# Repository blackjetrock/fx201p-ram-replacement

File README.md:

# fx201p-ram-replacement
FX201P RAM replacement

A PCB that replaces the RAM in an FX201P. Both HD36106 devices are replaced by an RP2040 based Pico-Zero
module. That replaces the memories and the program RAM. Additional features are added:

* Save program space to RP2040 internal flash
* Load program space from flash
* Save memory space to flash
* Load memory space from flash
* Save all memory to flash
* Load all memory from flash
* Catalog of flash slots.

  The flash has 250 slots, each is big enough to hold the entire RAM of the FX201P.

Command Mechanism
=================

To issue a command to the RP2040, put a number of the following format in M8:

ccsnnn E88

where:
```
cc     Command code
s      Status
nnn    Parameter
```

Command codes:

```
94          Zero all memory (both HD356106 RAM areas, but not flash)
95          Zero memories
96          Zero program space

11          Load program and memory areas from flash slot nnn
12          Load memory area from slot nnn
13          Load program area from slot nnn

15          Save program and memory areas to flash slot nnn
16          Save memory area to flash slot nnn
17          Save program area to flash slot nnn

47          Shows empty flash slots as a bitmap in octal in M9 A 1 denotes a non-blank slot
```

USB Interface
=============

The USB of the Pio-Zero has a menu driven interface.

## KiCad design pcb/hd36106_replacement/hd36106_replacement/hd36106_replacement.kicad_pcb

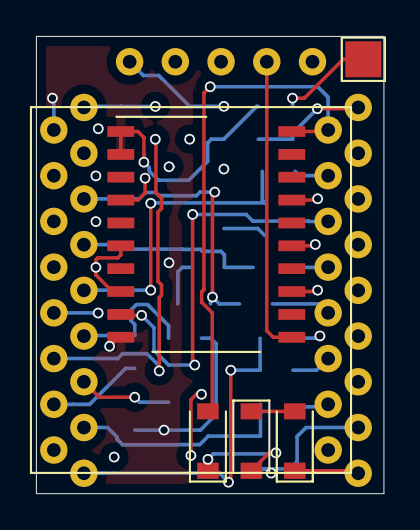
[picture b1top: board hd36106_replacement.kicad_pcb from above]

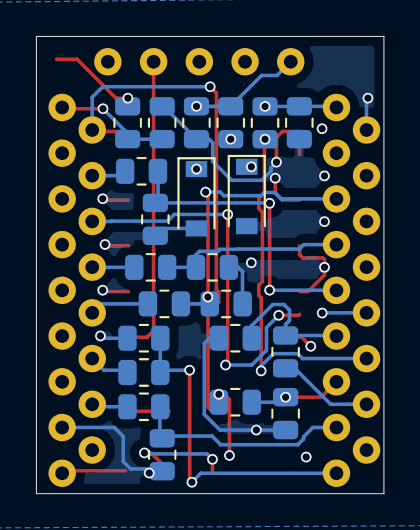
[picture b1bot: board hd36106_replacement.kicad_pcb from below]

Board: 4 copper layers, 19.3 x 25.4 mm, 29 parts (22 on the bottom side), 27 nets.

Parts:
D1: 4148; D_SOD-123
D2, D3: Schottky; D_SOD-123
D4, D5: SS36; D_SOD-123
J1: Conn_01x01_Male; TestPoint_Pad_2.0x2.0mm
R1, R2, R3, R4, R5, R6, R7, R8, R9, R10, R11, R12, R13, R14, R15, R16, R17, R18: 10k; R_0805_2012Metric
R27, R28: R_Small; R_0805_2012Metric
U1: rp2040-zero
U2: 40244; SO-20_12.8x7.5mm_P1.27mm
U3: HD36106; tc5006p

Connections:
6V4: D1.2, U2.20, U3.16
A0: R3.2, R4.1, U1.23
A1: R1.2, R2.1, U1.22
A2: R13.2, R14.1, U1.21
A3: R11.2, R12.1, U1.20
CE: R5.2, R6.1, U1.17
CE2: R27.2, R28.1, U1.9
CLKA: D4.1, R7.2, R8.1, U1.14
CLKB: D5.1, R9.2, R10.1, U1.15
DIN: R17.2, R18.1, U1.19
DOUT_HD36106: U2.9, U3.14
DOUT_PICO: U1.11, U2.11
GND: D4.2, D5.2, R2.2, R4.2, R6.2, R8.2, R10.2, R12.2, R14.2, R16.2, R18.2, R28.2, U1.2, U2.1, U2.2, U2.4, U2.6, U2.8, U2.10, U2.13, U2.15, U2.17, U3.1
unnamed: D1.1, D2.2
unnamed: D2.1, D3.2
unnamed: D3.1, U1.1
unnamed: J1.1, R27.1
unnamed: R1.1, U3.10
unnamed: R3.1, U3.11
unnamed: R5.1, U3.12
unnamed: R7.1, U3.5
unnamed: R9.1, U3.6
unnamed: R11.1, U3.7
unnamed: R13.1, U3.9
unnamed: R15.1, U3.13
unnamed: R17.1, U3.15
RW: R15.2, R16.1, U1.18
